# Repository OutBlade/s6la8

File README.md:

# s6la8

An open-source 8-channel logic analyzer built around a Cypress/Infineon
CY7C68013A (FX2LP) USB controller and a Xilinx Spartan-6 XC6SLX9 FPGA, with a
driver for [sigrok](https://sigrok.org).

`s6la8` is a working name.

## Status: design complete, not yet built or tested on hardware

The design files are complete and pass every check that can run without
hardware. No board has been manufactured and no bitstream has been built yet,
so **build and test prototypes before ordering a batch** (see
[docs/manufacturing.md](docs/manufacturing.md)).

| Part | State |
|---|---|
| Schematic (`hardware/s6la8.zen`) | Complete, 155 parts. KiCad ERC: 0 errors; 7 "power pin not driven" findings are downgraded to warnings in the project file because the rails are fed by regulator outputs and the generated sheet has no power flags. Not yet reviewed by a second person |
| PCB layout (`hardware/eda/s6la8.kicad_pcb`) | **Fully routed. KiCad DRC: 0 errors, 0 unconnected, 1 warning** (the probe header's silkscreen was trimmed at the board edge on purpose). Schematic parity: only naming differences. USB pair routed as a coupled 90 ohm pair. No signal- or power-integrity simulation |
| Manufacturing package (`hardware/release.py`) | Gerbers, drill, JLCPCB BOM and pick-and-place, STEP, schematic and assembly PDFs, fab notes. Refuses to build unless DRC is clean |
| Enclosure (`case/`) | Printable tray and lid (OpenSCAD), checked against KiCad's 3D model of the populated board: no collisions. Not yet printed |
| FX2 firmware (`firmware/`) | Compiles with SDCC (4.0 KB of code). Never run |
| FPGA gateware (`gateware/`) | Streaming, triggered capture into block RAM (32 K samples) or SDRAM (32 M samples), and board authentication pass simulation, the SDRAM against a model that checks the datasheet timing; Verilator lint clean; Yosys estimate 45 % of the LUTs. **No ISE build yet**, so pinout and timing are unverified |
| libsigrok driver (`host/driver/`) | Compiles against libsigrok. Never run against a device |
| Production tools (`tools/`) | Key generation, per-board provisioning and end-of-line test. Never run against a device |

The schematic is in [docs/schematic.pdf](docs/schematic.pdf): one large
generated sheet (2.7 x 1 m), best read zoomed in on screen.

## Design

- 8 channels through a 74LVC8T245 whose input side runs from the target's own
  supply (1.65 V to 5.5 V), with series resistors and ESD protection.
- XC6SLX9 samples, triggers (four stages, level and edge) and buffers.
- FX2LP carries data over USB 2.0 high speed in synchronous slave-FIFO mode,
  loads the FPGA bitstream (slave serial) and gives the host register access.
- 256 Mbit SDRAM as a 32 M-sample deep buffer at up to 100 MS/s; the
  driver uses it automatically for captures over 32 K samples.
- Fallback: a 74LVC245 copies the buffered probes onto FX2 port B, so the
  board is intended to work as a plain 24 MS/s `fx2lafw` analyzer with any
  released sigrok, with the FPGA unconfigured.

Rates implemented in gateware: up to 100 MS/s into the buffer, up to 25 MS/s
streaming. 200 MS/s is a goal, not a feature.

## Layout

The board is 100 x 64 mm, four layers (signal / GND / 3.3 V / signal). The
flow is scripted and repeatable:

```
pcb layout hardware/s6la8.zen          # sync footprints and nets (Zener)
python layout/place.py eda/s6la8.kicad_pcb     # seed placement
python layout/route.py eda/s6la8.kicad_pcb     # Freerouting
python layout/fanout.py eda/s6la8.kicad_pcb    # plane vias
python layout/patch.py dump|rip|apply ...      # leftovers, see the file header
python layout/patch_solve.py ...               # grid router with rip-up (needs numpy)
```

(`place.py`, `route.py`, `fanout.py` and `patch.py` run with KiCad's bundled
Python.)

The leftover pass is a plain grid router. It closed the connections
Freerouting left open by cutting neighbouring tracks near a boxed-in pad and
joining them again around the new copper. The tracks it lays are legal but
not pretty (many short 0.05 mm jogs), and it moved parts of `FD1`, `FD4`,
`FD7`, `FLAGA`, `SLOE`, `MODE`, `SD_BA0`, `SD_DQ1` and `SD_DQ12` without any
regard for length or impedance.

`layout/usb_pair.py` re-routes the USB pair as a coupled pair and
`layout/silk.py` sets up the production silkscreen; both can run again after
`pcb layout`.

The leftover pass is a plain grid router. It closed the connections
Freerouting left open by cutting neighbouring tracks near a boxed-in pad and
joining them again around the new copper. One pin (FPGA pin 54, GND) needed a
placement change: decoupling capacitors C40 (1.2 V) and C46 (3.3 V) swapped
places so that the 1.2 V track no longer crosses the ground pin's exit. The
grid router's tracks are legal but not pretty, and it moved parts of `FD1`,
`FD4`, `FD7`, `FLAGA`, `PKTEND`, `SLOE`, `MODE`, `SD_BA0`, `SD_DQ1` and
`SD_DQ12` without regard for length; none of these is critical at the rates
implemented.

Before ordering a batch:

1. Build the gateware in Xilinx ISE and confirm the pinout and timing.
2. Build five prototypes and run the bring-up list in
   [docs/manufacturing.md](docs/manufacturing.md).
3. Check every footprint against the datasheet of the exact part ordered.

## Copy protection

The FPGA bitstream checks that it runs on a board you provisioned:

- Every Spartan-6 has a factory-programmed, unique 57-bit Device DNA.
  (The XC6SLX9 has no bitstream encryption; only the LX75 and larger do.)
- At the end-of-line test, `tools/eol.py` reads the DNA and writes
  SipHash-2-4(key, DNA) into the EEPROM. The key is 128 bits from
  `tools/provision.py newkey` and never leaves your machine.
- A production bitstream (`make -C gateware/ise bitstream PRODUCTION=1`)
  contains the key, recomputes the hash and refuses to capture if it does
  not match. The sigrok driver says so plainly.
- A cloned board has a different DNA. Making it work needs the key, which
  means reverse-engineering the undocumented Spartan-6 bitstream format, or
  patching the check out of the bitstream. Both are possible for a determined
  expert but far beyond copying a PCB.

**Limits, and a decision for you.** This repository is published under GPL and
CERN-OHL-S, which explicitly allow anyone to build and sell copies. The open
default build (`auth_key_dev.vh`) does not enforce the check, so a cloner can
simply build their own unrestricted bitstream from this repository. The
scheme only protects your product if the production gateware and key stay
private: keep `gateware/` (you are its sole author, so you may relicense it)
and the key out of public repositories from now on, and protect the product
name with a trademark. The firmware is derived from fx2lafw and stays
GPL-2.0; the libsigrok driver stays GPL-3.0.

## Manufacturing

```
python hardware/release.py A      # -> hardware/release/revA/
```

Cost, supplier choice, import and the German legal requirements (CE, WEEE,
packaging) for a run of 100 are in [docs/manufacturing.md](docs/manufacturing.md).
The enclosure is in [case/](case/s6la8_case.scad): PETG, no supports, four
M3x12 screws into heat-set inserts.

## Building

Everything except the bitstream builds in the development container:

```
./dev.sh make -C firmware             # FX2 firmware -> firmware/build/s6la8-fx2.fw
./dev.sh make -C gateware sim lint    # simulation and lint
./dev.sh bash host/build.sh           # libsigrok with the s6la8 driver
```

On PowerShell use `.\dev.ps1` instead of `./dev.sh`.

The bitstream needs Xilinx ISE 14.7 WebPACK, which is x86-64 only (there is
no open-source place-and-route for Spartan-6). On an x86-64 machine:

```
make -C gateware/ise bitstream            # PRODUCTION=1 for the locked build
```

On an Arm machine the same build runs in an x86-64 container; see
[gateware/ise/README-docker.md](gateware/ise/README-docker.md).

The hardware is described in [Zener](https://github.com/diodeinc/pcb) and
generates a KiCad 10 project in `hardware/eda/`. `hardware/gen_pins.py`
derives the FPGA pin constraints from the schematic.

## USB identity

The firmware currently uses the pid.codes test ID `1209:0001`. That is for
development only and must be replaced by an assigned ID before any board is
distributed.

## Licenses

| Part | License |
|---|---|
| `host/driver/`, `gateware/` | GPL-3.0-or-later |
| `firmware/` | GPL-2.0-or-later (derived from sigrok-firmware-fx2lafw); bundled fx2lib is LGPL-2.1-or-later |
| `hardware/` | CERN-OHL-S-2.0 |
| `hardware/lib/` | Symbols and footprints copied from the KiCad libraries (CC-BY-SA 4.0 with the KiCad library exception) |

Full texts are in `LICENSES/`.

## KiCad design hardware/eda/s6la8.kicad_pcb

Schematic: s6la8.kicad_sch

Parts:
C1, C4, C29: 10uF 10V; C_0805_2012Metric
C2, C3, C5, C6: 22uF 6.3V; C_0805_2012Metric
C7, C9, C10, C11, C12, C13, C14, C15, C16, C17, C20, C21, C22, C23, C24, C25, C26, C27, C31, C32, C33, C34, C35, C39, C40, C41, C42, C43, C45, C46, C47, C48, C49, C50, C51, C52, C53, C54, C55: 100nF 6.3V; C_0402_1005Metric
C8: 2.2uF 6.3V; C_0603_1608Metric
C18, C36, C44: 4.7uF 6.3V; C_0805_2012Metric
C19: 1uF; C_0402_1005Metric
C28, C56: 10uF 6.3V; C_0805_2012Metric
C30, C37: 100nF 10V; C_0402_1005Metric
C38: 1uF 10V; C_0402_1005Metric
C57, C58: 18pF; C_0402_1005Metric
D1, D3: LED GREEN; LED_0603_1608Metric
D2: LED RED; LED_0603_1608Metric
D4: LED YELLOW; LED_0603_1608Metric
FB1: 220 100MHz; R_0603_1608Metric
FB2: 220 100MHz; R_0805_2012Metric
FID1, FID2, FID3: Fiducial; Fiducial_1mm_Mask2mm
H1, H2, H3, H4: M3 DIN965 TopBottom; MountingHole_3.2mm_M3_DIN965_Pad_TopBottom
J1: 2.54mm 6 x 1 THT Vertical Male; PinHeader_1x06_P2.54mm_Vertical
J2: 2.54mm 2 x 1 THT Vertical Male; PinHeader_1x02_P2.54mm_Vertical
J3: 2.54mm 10 x 2 THT Horizontal Male; PinHeader_2x10_P2.54mm_Horizontal
J4: USB4105-GF-A; USB_C_Receptacle_GCT_USB4105-xx-A_16P_TopMnt_Horizontal
J5: 2.54mm 3 x 1 THT Vertical Male; PinHeader_1x03_P2.54mm_Vertical
L1, L2: 2.2uH; L_1210_3225Metric
R1, R2, R3, R9, R11, R13, R15, R17, R19, R21, R23, R28, R40, R61: 100k; R_0402_1005Metric
R4: 453k; R_0402_1005Metric
R5, R6: 5.1k; R_0402_1005Metric
R7, R24, R29, R30, R31, R32, R33, R34, R35, R36, R43: 33; R_0402_1005Metric
R8, R10, R12, R14, R16, R18, R20, R22, R27, R60: 100; R_0402_1005Metric
R25, R42, R45, R46, R47, R48, R54: 1k; R_0402_1005Metric
R26: 330; R_0402_1005Metric
R37, R38, R39, R41, R51, R52, R57, R58, R59: 10k; R_0402_1005Metric
R44, R49, R50, R53: 4.7k; R_0402_1005Metric
R55, R56: 2.2k; R_0402_1005Metric
U1: 24LC128-I/SN; SOIC-8_3.9x4.9mm_P1.27mm
U2, U3, U4, U5, U6: USBLC6-2SC6; SOT-23-6
U7: SN74LVC245APWR; TSSOP-20_4.4x6.5mm_P0.65mm
U8: SN74LVC8T245PWR; TSSOP-24_4.4x7.8mm_P0.65mm
U9: SN74LVC2T45DCUR; VSSOP-8_2.3x2mm_P0.5mm
U10: XC6SLX9-2TQG144C; TQFP-144_20x20mm_P0.5mm
U11: CY7C68013A-56PVXC; SSOP-56_7.5x18.5mm_P0.635mm
U12, U13: TLV62569DBVR; SOT-23-5
U14: MT48LC16M16A2P-6A; TSOP-II-54_22.2x10.16mm_P0.8mm
Y1: ASE-50.000MHZ-LC-T; Oscillator_SMD_Abracon_ASE-4Pin_3.2x2.5mm
Y2: 24MHz 12pF; Crystal_SMD_3225-4Pin_3.2x2.5mm

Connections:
AVCC: C7.1, C8.1, FB1.2, U11.10 (AVCC), U11.14 (AVCC)
CC1: J4.A5 (CC1), R5.1
CC2: J4.B5 (CC2), R6.1
CCLK: R7.2, U10.70 (IO_L1P_CCLK_2)
CCLK_SRC: R7.1, U11.56 (PD4/FD12)
CH0: U7.2 (A1), U8.21 (B1), U10.5 (IO_L52N_3)
CH0_A: R8.2, R9.1, U2.1 (I/O1), U2.6 (I/O1), U8.3 (A1)
CH0_IN: J3.1, R8.1
CH1: U7.3 (A2), U8.20 (B2), U10.6 (IO_L52P_3)
CH1_A: R10.2, R11.1, U2.3 (I/O2), U2.4 (I/O2), U8.4 (A2)
CH1_IN: J3.3, R10.1
CH2: U7.4 (A3), U8.19 (B3), U10.7 (IO_L51N_3)
CH2_A: R12.2, R13.1, U3.1 (I/O1), U3.6 (I/O1), U8.5 (A3)
CH2_IN: J3.5, R12.1
CH3: U7.5 (A4), U8.18 (B4), U10.8 (IO_L51P_3)
CH3_A: R14.2, R15.1, U3.3 (I/O2), U3.4 (I/O2), U8.6 (A4)
CH3_IN: J3.7, R14.1
CH4: U7.6 (A5), U8.17 (B5), U10.9 (IO_L50N_3)
CH4_A: R16.2, R17.1, U4.1 (I/O1), U4.6 (I/O1), U8.7 (A5)
CH4_IN: J3.9, R16.1
CH5: U7.7 (A6), U8.16 (B6), U10.10 (IO_L50P_3)
CH5_A: R18.2, R19.1, U4.3 (I/O2), U4.4 (I/O2), U8.8 (A6)
CH5_IN: J3.11, R18.1
CH6: U7.8 (A7), U8.15 (B7), U10.11 (IO_L49N_3)
CH6_A: R20.2, R21.1, U5.1 (I/O1), U5.6 (I/O1), U8.9 (A7)
CH6_IN: J3.13, R20.1
CH7: U7.9 (A8), U8.14 (B8), U10.12 (IO_L49P_3)
CH7_A: R22.2, R23.1, U5.3 (I/O2), U5.4 (I/O2), U8.10 (A8)
CH7_IN: J3.15, R22.1
CLK50: R24.2, U10.15 (IO_L44P_GCLK21_3)
CLK50_SRC: R24.1, Y1.3 (OUT)
CSI_B: R25.1, U10.64 (IO_L3N_MOSI_CSI_B_MISO0_2)
DONE: R26.2, U10.71 (DONE_2), U11.54 (PD2/FD10)
EXT_CLK: U9.7 (B1), U10.17 (IO_L43P_GCLK23_3)
EXT_CLK_A: R27.2, R28.1, U9.2 (A1)
EXT_CLK_IN: J3.19, R27.1
FB0: R29.1, U7.18 (B1)
FB1: R30.1, U7.17 (B2)
FB2: R31.1, U7.16 (B3)
FB3: R32.1, U7.15 (B4)
FB4: R33.1, U7.14 (B5)
FB5: R34.1, U7.13 (B6)
FB6: R35.1, U7.12 (B7)
FB7: R36.1, U7.11 (B8)
FB_1V2: R1.1, R2.2, U12.5 (FB)
FB_3V3: R3.1, R4.2, U13.5 (FB)
FB_OE_N: R37.1, U7.19 (~OE), U10.30 (IO_L36P_3), U11.43 (PA3/WU2)
FD0: R29.2, U10.48 (IO_L48P_D7_2), U11.25 (PB0/FD0)
FD1: R30.2, U10.43 (IO_L62N_D6_2), U11.26 (PB1/FD1)
FD2: R31.2, U10.44 (IO_L62P_D5_2), U11.27 (PB2/FD2)
FD3: R32.2, U10.45 (IO_L49N_D4_2), U11.28 (PB3/FD3)
FD4: R33.2, U10.46 (IO_L49P_D3_2), U11.29 (PB4/FD4)
FD5: R34.2, U10.61 (IO_L12N_D2_MISO3_2), U11.30 (PB5/FD5)
FD6: R35.2, U10.62 (IO_L12P_D1_MISO2_2), U11.31 (PB6/FD6)
FD7: R36.2, U10.65 (IO_L3P_D0_DIN_MISO_MISO1_2), U11.32 (PB7/FD7)
FIFOADR0: R38.1, U10.58 (IO_L14P_D11_2), U11.44 (PA4/FIOADDR0)
FIFOADR1: R39.1, U10.59 (IO_L13N_D10_2), U11.45 (PA5/FIOADDR1)
FLAGA: U10.51 (IO_L31P_GCLK31_D14_2), U11.36 (CTL0/FLAGA)
FLAGB: U10.56 (IO_L30P_GCLK1_D13_2), U11.37 (CTL1/FLAGB)
FLAGC: U10.57 (IO_L14N_D12_2), U11.38 (CTL2/FLAGC)
FPGA_IRQ_N: U10.26 (IO_L37N_3), U11.40 (PA0/~INT0)
FX2_RESET_N: C19.1, R40.2, U11.49 (~RESET)
FX2_WAKEUP: R41.2, U11.51 (WAKEUP)
GND: C1.2, C2.2, C3.2, C4.2, C5.2, C6.2, C7.2, C8.2, C9.2, C10.2, C11.2, C12.2, C13.2, C14.2, C15.2, C16.2, C17.2, C18.2, C19.2, C20.2, C21.2, C22.2, C23.2, C24.2, C25.2, C26.2, C27.2, C28.2, C29.2, C30.2, C31.2, C32.2, C33.2, C34.2, C35.2, C36.2, C37.2, C38.2, C39.2, C40.2, C41.2, C42.2, C43.2, C44.2, C45.2, C46.2, C47.2, C48.2, C49.2, C50.2, C51.2, C52.2, C53.2, C54.2, C55.2, C56.2, C57.2, C58.2, D3.1 (K), D4.1 (K), H1.1, H2.1, H3.1, H4.1, J1.2, J2.2, J3.2, J3.4, J3.6, J3.8, J3.10, J3.12, J3.14, J3.16, J3.18, J4.A1 (GND), J4.A12 (GND), J4.B1 (GND), J4.B12 (GND), J4.SH (SHIELD), R1.2, R3.2, R5.2, R6.2, R9.2, R11.2, R13.2, R15.2, R17.2, R19.2, R21.2, R23.2, R25.2, R28.2, R37.2, R38.2, R39.2, R42.2, R54.2, R61.2, U1.2 (A1), U1.3 (A2), U1.4 (GND), U1.7 (WP), U2.2 (GND), U3.2 (GND), U4.2 (GND), U5.2 (GND), U6.2 (GND), U7.10 (GND), U8.11 (GND), U8.12 (GND), U8.13 (GND), U8.22 (~OE), U9.4 (GND), U10.3 (GND), U10.13 (GND), U10.25 (GND), U10.49 (GND), U10.54 (GND), U10.68 (GND), U10.73 (SUSPEND), U10.77 (GND), U10.91 (GND), U10.96 (GND), U10.108 (GND), U10.113 (GND), U10.130 (GND), U10.136 (GND), U11.4 (GND), U11.7 (GND), U11.13 (AGND), U11.17 (AGND), U11.19 (GND), U11.21 (RESERVED), U11.33 (GND), U11.35 (GND), U11.48 (GND), U12.2 (GND), U13.2 (GND), U14.6 (VSSQ), U14.12 (VSSQ), U14.28 (VSS), U14.41 (VSS), U14.46 (VSSQ), U14.52 (VSSQ), U14.54 (VSS), Y1.2 (GND), Y2.2 (G), Y2.4 (G)
HSWAPEN: R42.1, U10.144 (IO_L1P_HSWAPEN_0)
IFCLK: R43.2, U10.55 (IO_L30N_GCLK0_USERCCLK_2)
IFCLK_SRC: R43.1, U11.20 (IFCLK)
INIT_B: R44.2, U10.39 (IO_L65P_INIT_B_2), U11.53 (PD1/FD9)
LED1_A: D1.2 (A), R45.2
LED1_K: D1.1 (K), U10.29 (IO_L36N_3)
LED2_A: D2.2 (A), R46.2
LED2_K: D2.1 (K), U10.33 (IO_L2P_3)
LED_PWR_A: D3.2 (A), R47.2
LED_USB: R48.1, U11.41 (PA1/~INT1)
LED_USB_A: D4.2 (A), R48.2
M0: R49.2, U10.69 (IO_L1N_M0_CMPMISO_2), U11.55 (PD3/FD11)
M1: R50.2, U10.60 (IO_L13P_M1_2)
MODE: J2.1, R51.2, U11.47 (PA7/FLAGD/~SLCS)
NC_J_USB_SBU1: J4.A8 (SBU1)
NC_J_USB_SBU2: J4.B8 (SBU2)
NC_U_FPGA_CMPCS_B_2: U10.72 (CMPCS_B_2)
NC_U_FPGA_IO_L1N_VREF_0: U10.143 (IO_L1N_VREF_0)
NC_U_FPGA_IO_L1N_VREF_3: U10.34 (IO_L1N_VREF_3)
NC_U_FPGA_IO_L1P_3: U10.35 (IO_L1P_3)
NC_U_FPGA_IO_L2N_0: U10.141 (IO_L2N_0)
NC_U_FPGA_IO_L2N_3: U10.32 (IO_L2N_3)
NC_U_FPGA_IO_L2P_0: U10.142 (IO_L2P_0)
NC_U_FPGA_IO_L3N_0: U10.139 (IO_L3N_0)
NC_U_FPGA_IO_L3P_0: U10.140 (IO_L3P_0)
NC_U_FPGA_IO_L4P_0: U10.138 (IO_L4P_0)
NC_U_FPGA_IO_L41N_GCLK26_3: U10.23 (IO_L41N_GCLK26_3)
NC_U_FPGA_IO_L41P_GCLK27_3: U10.24 (IO_L41P_GCLK27_3)
NC_U_FPGA_IO_L42N_GCLK24_3: U10.21 (IO_L42N_GCLK24_3)
NC_U_FPGA_IO_L43N_GCLK22_IRDY2_3: U10.16 (IO_L43N_GCLK22_IRDY2_3)
NC_U_FPGA_IO_L44N_GCLK20_3: U10.14 (IO_L44N_GCLK20_3)
NC_U_FPGA_IO_L47N_1: U10.78 (IO_L47N_1)
NC_U_FPGA_IO_L47P_1: U10.79 (IO_L47P_1)
NC_U_FPGA_IO_L74N_DOUT_BUSY_1: U10.74 (IO_L74N_DOUT_BUSY_1)
NC_U_FPGA_IO_L74P_AWAKE_1: U10.75 (IO_L74P_AWAKE_1)
NC_U_FPGA_IO_L83N_VREF_3: U10.1 (IO_L83N_VREF_3)
NC_U_FPGA_IO_L83P_3: U10.2 (IO_L83P_3)
NC_U_FX2_CLKOUT: U11.5 (CLKOUT)
NC_U_SDRAM_NC: U14.40 (NC)
PKTEND: R52.2, U10.50 (IO_L31N_GCLK30_D15_2), U11.46 (PA6/PKTEND)
PROGRAM_B: R53.2, U10.37 (PROGRAM_B_2), U11.52 (PD0/FD8)
RDWR_B: R54.1, U10.47 (IO_L48N_RDWR_B_VREF_2)
REG_CS_N: U10.67 (IO_L2P_CMPCLK_2), U11.3 (PD7/FD15)
REG_MISO: U10.27 (IO_L37P_3), U11.2 (PD6/FD14)
REG_MOSI: U10.66 (IO_L2N_CMPMOSI_2), U11.1 (PD5/FD13)
SCL: R55.2, U1.6 (SCL), U11.22 (SCL)
SDA: R56.2, U1.5 (SDA), U11.23 (SDA)
SD_A0: U10.83 (IO_L45P_1), U14.23 (A0)
SD_A1: U10.82 (IO_L45N_1), U14.24 (A1)
SD_A2: U10.81 (IO_L46P_1), U14.25 (A2)
SD_A3: U10.80 (IO_L46N_1), U14.26 (A3)
SD_A4: U10.137 (IO_L4N_0), U14.29 (A4)
SD_A5: U10.134 (IO_L34P_GCLK19_0), U14.30 (A5)
SD_A6: U10.133 (IO_L34N_GCLK18_0), U14.31 (A6)
SD_A7: U10.132 (IO_L35P_GCLK17_0), U14.32 (A7)
SD_A8: U10.131 (IO_L35N_GCLK16_0), U14.33 (A8)
SD_A9: U10.127 (IO_L36P_GCLK15_0), U14.34 (A9)
SD_A10: U10.84 (IO_L43N_GCLK4_1), U14.22 (A10)
SD_A11: U10.126 (IO_L36N_GCLK14_0), U14.35 (A11)
SD_A12: U10.124 (IO_L37P_GCLK13_0), U14.36 (A12)
SD_BA0: U10.87 (IO_L42N_GCLK6_TRDY1_1), U14.20 (BA0)
SD_BA1: U10.85 (IO_L43P_GCLK5_1), U14.21 (BA1)
SD_CAS_N: U10.93 (IO_L41P_GCLK9_IRDY1_1), U14.17 (~CAS)
SD_CKE: U10.123 (IO_L37N_GCLK12_0), U14.37 (CKE)
SD_CLK: U10.121 (IO_L62P_0), U14.38 (CLK)
SD_CS_N: U10.88 (IO_L42P_GCLK7_1), U14.19 (~CS)
SD_DQ0: U10.105 (IO_L1P_1), U14.2 (DQ0)
SD_DQ1: U10.104 (IO_L1N_VREF_1), U14.4 (DQ1)
SD_DQ2: U10.102 (IO_L32P_1), U14.5 (DQ2)
SD_DQ3: U10.101 (IO_L32N_1), U14.7 (DQ3)
SD_DQ4: U10.100 (IO_L33P_1), U14.8 (DQ4)
SD_DQ5: U10.99 (IO_L33N_1), U14.10 (DQ5)
SD_DQ6: U10.98 (IO_L34P_1), U14.11 (DQ6)
SD_DQ7: U10.97 (IO_L34N_1), U14.13 (DQ7)
SD_DQ8: U10.119 (IO_L63P_SCP7_0), U14.42 (DQ8)
SD_DQ9: U10.118 (IO_L63N_SCP6_0), U14.44 (DQ9)
SD_DQ10: U10.117 (IO_L64P_SCP5_0), U14.45 (DQ10)
SD_DQ11: U10.116 (IO_L64N_SCP4_0), U14.47 (DQ11)
SD_DQ12: U10.115 (IO_L65P_SCP3_0), U14.48 (DQ12)
SD_DQ13: U10.114 (IO_L65N_SCP2_0), U14.50 (DQ13)
SD_DQ14: U10.112 (IO_L66P_SCP1_0), U14.51 (DQ14)
SD_DQ15: U10.111 (IO_L66N_SCP0_0), U14.53 (DQ15)
SD_DQMH: U10.120 (IO_L62N_VREF_0), U14.39 (DQMH)
SD_DQML: U10.95 (IO_L40P_GCLK11_1), U14.15 (DQML)
SD_RAS_N: U10.92 (IO_L41N_GCLK8_1), U14.18 (~RAS)
SD_WE_N: U10.94 (IO_L40N_GCLK10_1), U14.16 (~WE)
SLOE: R57.2, U10.41 (IO_L64P_D8_2), U11.42 (PA2/SLOE)
SLRD: R58.2, U10.40 (IO_L64N_D9_2), U11.8 (RDY0/SLRD)
SLWR: R59.2, U10.38 (IO_L65N_CSO_B_2), U11.9 (RDY1/SLWR)
SW_1V2: L1.1, U12.3 (SW)
SW_3V3: L2.1, U13.3 (SW)
TCK: J1.3, U10.109 (TCK)
TDI: J1.5, U10.110 (TDI)
TDO: J1.4, U10.106 (TDO)
TMS: J1.6, U10.107 (TMS)
TRIG: U9.6 (B2), U10.22 (IO_L42P_GCLK25_TRDY2_3)
TRIG_A: R60.2, R61.1, U9.3 (A2)
TRIG_IN: J3.20, R60.1
USB_D_N: J4.A7 (D-), J4.B7 (D-), U6.3 (I/O2), U6.4 (I/O2), U11.16 (D-)
USB_D_P: J4.A6 (D+), J4.B6 (D+), U6.1 (I/O1), U6.6 (I/O1), U11.15 (D+)
V5: C1.1, C4.1, C29.1, C30.1, FB2.2, U12.1 (EN), U12.4 (VIN), U13.1 (EN), U13.4 (VIN)
VBUS: FB2.1, J4.A4 (VBUS), J4.A9 (VBUS), J4.B4 (VBUS), J4.B9 (VBUS), U6.5 (VBUS)
VCCA: C37.1, C38.1, J5.2, U2.5 (VBUS), U3.5 (VBUS), U4.5 (VBUS), U5.5 (VBUS), U8.1 (V_{CCA}), U8.2 (DIR), U9.1 (VCCA), U9.5 (DIR)
VCC_1V2: C2.1, C3.1, C39.1, C40.1, C41.1, C42.1, C43.1, C44.1, L1.2, R2.1, U10.19 (VCCINT), U10.28 (VCCINT), U10.52 (VCCINT), U10.89 (VCCINT), U10.128 (VCCINT)
VCC_3V3: C5.1, C6.1, C9.1, C10.1, C11.1, C12.1, C13.1, C14.1, C15.1, C16.1, C17.1, C18.1, C20.1, C21.1, C22.1, C23.1, C24.1, C25.1, C26.1, C27.1, C28.1, C31.1, C32.1, C33.1, C34.1, C35.1, C36.1, C45.1, C46.1, C47.1, C48.1, C49.1, C50.1, C51.1, C52.1, C53.1, C54.1, C55.1, C56.1, FB1.1, J1.1, J5.3, L2.2, R4.1, R26.1, R40.1, R41.1, R44.1, R45.1, R46.1, R47.1, R49.1, R50.1, R51.1, R52.1, R53.1, R55.1, R56.1, R57.1, R58.1, R59.1, U1.1 (A0), U1.8 (VCC), U7.1 (DIR), U7.20 (VCC), U8.23 (V_{CCB}), U8.24 (V_{CCB}), U9.8 (VCCB), U10.4 (VCCO_3), U10.18 (VCCO_3), U10.20 (VCCAUX), U10.31 (VCCO_3), U10.36 (VCCAUX), U10.42 (VCCO_2), U10.53 (VCCAUX), U10.63 (VCCO_2), U10.76 (VCCO_1), U10.86 (VCCO_1), U10.90 (VCCAUX), U10.103 (VCCO_1), U10.122 (VCCO_0), U10.125 (VCCO_0), U10.129 (VCCAUX), U10.135 (VCCO_0), U11.6 (VCC), U11.18 (VCC), U11.24 (VCC), U11.34 (VCC), U11.39 (VCC), U11.50 (VCC), U14.1 (VDD), U14.3 (VDDQ), U14.9 (VDDQ), U14.14 (VDD), U14.27 (VDD), U14.43 (VDDQ), U14.49 (VDDQ), Y1.1 (EN), Y1.4 (Vdd)
VREF_T: J3.17, J5.1
XTALIN: C57.1, U11.12 (XTALIN), Y2.1
XTALOUT: C58.1, U11.11 (XTALOUT), Y2.3

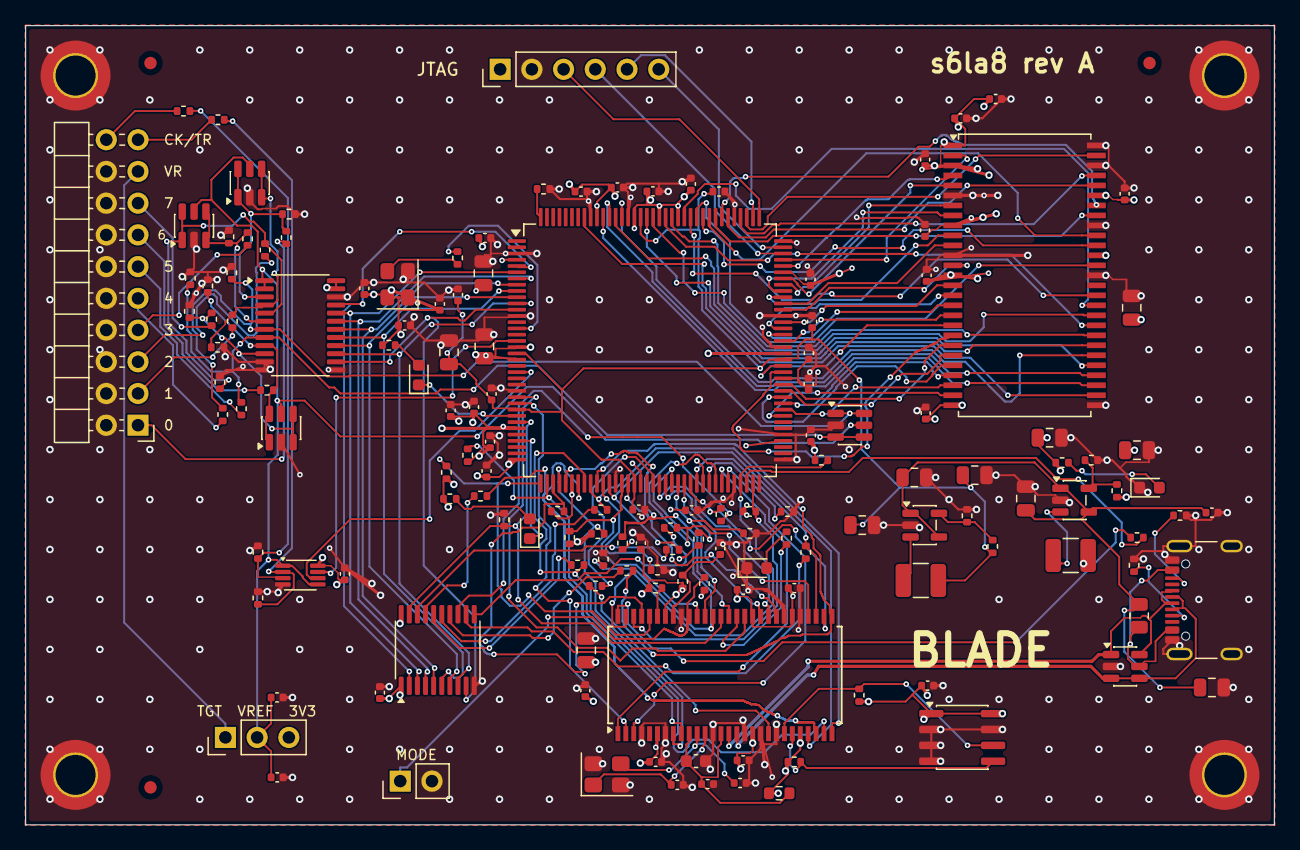
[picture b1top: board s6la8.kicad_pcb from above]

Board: 4 copper layers, 100.0 x 64.0 mm, 155 parts (0 on the bottom side), 147 nets.

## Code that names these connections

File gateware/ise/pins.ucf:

# Generated by hardware/gen_pins.py from the schematic. Do not edit.
CONFIG VCCAUX = "3.3";

NET "CCLK" LOC = P70 | IOSTANDARD = LVCMOS33;
NET "CH<0>" LOC = P5 | IOSTANDARD = LVCMOS33;
NET "CH<1>" LOC = P6 | IOSTANDARD = LVCMOS33;
NET "CH<2>" LOC = P7 | IOSTANDARD = LVCMOS33;
NET "CH<3>" LOC = P8 | IOSTANDARD = LVCMOS33;
NET "CH<4>" LOC = P9 | IOSTANDARD = LVCMOS33;
NET "CH<5>" LOC = P10 | IOSTANDARD = LVCMOS33;
NET "CH<6>" LOC = P11 | IOSTANDARD = LVCMOS33;
NET "CH<7>" LOC = P12 | IOSTANDARD = LVCMOS33;
NET "CLK50" LOC = P15 | IOSTANDARD = LVCMOS33;
NET "EXT_CLK" LOC = P17 | IOSTANDARD = LVCMOS33;
NET "FB_OE_N" LOC = P30 | IOSTANDARD = LVCMOS33;
NET "FD<0>" LOC = P48 | IOSTANDARD = LVCMOS33;
NET "FD<1>" LOC = P43 | IOSTANDARD = LVCMOS33;
NET "FD<2>" LOC = P44 | IOSTANDARD = LVCMOS33;
NET "FD<3>" LOC = P45 | IOSTANDARD = LVCMOS33;
NET "FD<4>" LOC = P46 | IOSTANDARD = LVCMOS33;
NET "FD<5>" LOC = P61 | IOSTANDARD = LVCMOS33;
NET "FD<6>" LOC = P62 | IOSTANDARD = LVCMOS33;
NET "FD<7>" LOC = P65 | IOSTANDARD = LVCMOS33;
NET "FIFOADR0" LOC = P58 | IOSTANDARD = LVCMOS33;
NET "FIFOADR1" LOC = P59 | IOSTANDARD = LVCMOS33;
NET "FLAGA" LOC = P51 | IOSTANDARD = LVCMOS33;
NET "FLAGB" LOC = P56 | IOSTANDARD = LVCMOS33;
NET "FLAGC" LOC = P57 | IOSTANDARD = LVCMOS33;
NET "FPGA_IRQ_N" LOC = P26 | IOSTANDARD = LVCMOS33;
NET "IFCLK" LOC = P55 | IOSTANDARD = LVCMOS33;
NET "LED1_K" LOC = P29 | IOSTANDARD = LVCMOS33;
NET "LED2_K" LOC = P33 | IOSTANDARD = LVCMOS33;
NET "PKTEND" LOC = P50 | IOSTANDARD = LVCMOS33;
NET "REG_CS_N" LOC = P67 | IOSTANDARD = LVCMOS33;
NET "REG_MISO" LOC = P27 | IOSTANDARD = LVCMOS33;
NET "REG_MOSI" LOC = P66 | IOSTANDARD = LVCMOS33;
NET "SD_A<0>" LOC = P83 | IOSTANDARD = LVCMOS33;
NET "SD_A<1>" LOC = P82 | IOSTANDARD = LVCMOS33;
NET "SD_A<2>" LOC = P81 | IOSTANDARD = LVCMOS33;
NET "SD_A<3>" LOC = P80 | IOSTANDARD = LVCMOS33;
NET "SD_A<4>" LOC = P137 | IOSTANDARD = LVCMOS33;
NET "SD_A<5>" LOC = P134 | IOSTANDARD = LVCMOS33;
NET "SD_A<6>" LOC = P133 | IOSTANDARD = LVCMOS33;
NET "SD_A<7>" LOC = P132 | IOSTANDARD = LVCMOS33;
NET "SD_A<8>" LOC = P131 | IOSTANDARD = LVCMOS33;
NET "SD_A<9>" LOC = P127 | IOSTANDARD = LVCMOS33;
NET "SD_A<10>" LOC = P84 | IOSTANDARD = LVCMOS33;
NET "SD_A<11>" LOC = P126 | IOSTANDARD = LVCMOS33;
NET "SD_A<12>" LOC = P124 | IOSTANDARD = LVCMOS33;
NET "SD_BA0" LOC = P87 | IOSTANDARD = LVCMOS33;
NET "SD_BA1" LOC = P85 | IOSTANDARD = LVCMOS33;
NET "SD_CAS_N" LOC = P93 | IOSTANDARD = LVCMOS33;
NET "SD_CKE" LOC = P123 | IOSTANDARD = LVCMOS33;
NET "SD_CLK" LOC = P121 | IOSTANDARD = LVCMOS33;
NET "SD_CS_N" LOC = P88 | IOSTANDARD = LVCMOS33;
NET "SD_DQ<0>" LOC = P105 | IOSTANDARD = LVCMOS33;
NET "SD_DQ<1>" LOC = P104 | IOSTANDARD = LVCMOS33;
NET "SD_DQ<2>" LOC = P102 | IOSTANDARD = LVCMOS33;
NET "SD_DQ<3>" LOC = P101 | IOSTANDARD = LVCMOS33;
NET "SD_DQ<4>" LOC = P100 | IOSTANDARD = LVCMOS33;
NET "SD_DQ<5>" LOC = P99 | IOSTANDARD = LVCMOS33;
NET "SD_DQ<6>" LOC = P98 | IOSTANDARD = LVCMOS33;
NET "SD_DQ<7>" LOC = P97 | IOSTANDARD = LVCMOS33;
NET "SD_DQ<8>" LOC = P119 | IOSTANDARD = LVCMOS33;
NET "SD_DQ<9>" LOC = P118 | IOSTANDARD = LVCMOS33;
NET "SD_DQ<10>" LOC = P117 | IOSTANDARD = LVCMOS33;
NET "SD_DQ<11>" LOC = P116 | IOSTANDARD = LVCMOS33;
NET "SD_DQ<12>" LOC = P115 | IOSTANDARD = LVCMOS33;
NET "SD_DQ<13>" LOC = P114 | IOSTANDARD = LVCMOS33;
NET "SD_DQ<14>" LOC = P112 | IOSTANDARD = LVCMOS33;
NET "SD_DQ<15>" LOC = P111 | IOSTANDARD = LVCMOS33;
NET "SD_DQMH" LOC = P120 | IOSTANDARD = LVCMOS33;
NET "SD_DQML" LOC = P95 | IOSTANDARD = LVCMOS33;
NET "SD_RAS_N" LOC = P92 | IOSTANDARD = LVCMOS33;
NET "SD_WE_N" LOC = P94 | IOSTANDARD = LVCMOS33;
NET "SLOE" LOC = P41 | IOSTANDARD = LVCMOS33;
NET "SLRD" LOC = P40 | IOSTANDARD = LVCMOS33;
NET "SLWR" LOC = P38 | IOSTANDARD = LVCMOS33;
NET "TRIG" LOC = P22 | IOSTANDARD = LVCMOS33;

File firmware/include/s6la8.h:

/*
 * This file is part of the s6la8 project.
 *
 * This program is free software; you can redistribute it and/or modify
 * it under the terms of the GNU General Public License as published by
 * the Free Software Foundation; either version 2 of the License, or
 * (at your option) any later version.
 */

#ifndef S6LA8_INCLUDE_S6LA8_H
#define S6LA8_INCLUDE_S6LA8_H

/*
 * Protocol version, returned by CMD_GET_FW_VERSION.  Major 2 distinguishes
 * this firmware from fx2lafw (major 1); bump major on incompatible changes.
 */
#define S6LA8_VERSION_MAJOR	2
#define S6LA8_VERSION_MINOR	0

/* Vendor requests beyond the fx2lafw ones in command.h. */
#define CMD_FPGA_CONFIG_BEGIN	0xc0	/* OUT, no data: reset FPGA, expect bitstream on EP6 */
#define CMD_FPGA_CONFIG_END	0xc1	/* IN, 1 byte: finish start-up, return status */
#define CMD_REG_WRITE		0xc2	/* OUT, wValue = address, data = bytes */
#define CMD_REG_READ		0xc3	/* IN, wValue = address, wLength = bytes */
#define CMD_ACQUISITION		0xc4	/* OUT, wValue = 1 start / 0 stop */
#define CMD_GET_STATUS		0xc5	/* IN, 1 byte */
#define CMD_EEPROM_WRITE	0xc6	/* OUT, wValue = EEPROM address, MODE jumper fitted */
#define CMD_EEPROM_READ		0xc7	/* IN, wValue = EEPROM address */

/* 24LC128 with A0 tied high; the authentication tag lives in its last page. */
#define EEPROM_ADDR		0x51
#define EEPROM_TAG_OFFSET	0x3f00

/* FPGA registers (gateware/rtl/top.v). */
#define REG_AUTH		0x06	/* write 1: check tag; read: bit1 ok, bit0 DNA read */
#define REG_AUTH_TAG		0x30	/* 8 bytes, little endian */
#define REG_DNA			0x38	/* 8 bytes, little endian, read only */

#define STATUS_DONE		(1 << 0)
#define STATUS_INIT_B		(1 << 1)
#define STATUS_IRQ		(1 << 2)
#define STATUS_MODE_JUMPER	(1 << 3)

/* Board wiring; must match hardware/s6la8.zen. */
#define FPGA_IRQ_N	PA0
#define LED		PA1	/* high = on, as in fx2lafw */
#define FB_OE_N		PA3	/* low = fallback buffer drives FD[7:0] */
#define MODE		PA7

#define DIN		PB7	/* FD7 is wired to the FPGA's D0/DIN */

#define PROGRAM_B	PD0
#define INIT_B		PD1
#define DONE		PD2
#define M0		PD3
#define CCLK		PD4
#define REG_SCK		PD4
#define REG_MOSI	PD5
#define REG_MISO	PD6
#define REG_CS_N	PD7

#endif
